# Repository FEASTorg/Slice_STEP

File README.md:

<div align="center">
  <!-- Title: -->
  
  <h2><a href="https://github.com/uwo-fast/Slice_STEP"> STEP Slice </a></h2>
  <!-- Labels: -->
  <!-- First row: -->

  <a href="https://certification.oshwa.org/">
    
    <!-- img src="https://img.shields.io/badge/OSHWA-Certified-darkgreen?style=flat-square" height="20" alt="OSHWA" -->       <!-- img src="https://img.shields.io/badge/OSHWA-Pending-darkorange?style=flat-square" height="20" alt="OSHWA" -->
  </a>

  <!-- Second row: -->
  <br>

  <!-- Short description: -->
  <h3>Stepper Motor Driver Carrier Slice for BREAD.</h3>
</div>

## Introduction
[Provide a brief introduction to the project, including the motivation and goals. Explain the significance and context of the research.]

## Project Overview
[Describe the project in more detail. This section can be split into subsections if necessary.]

## Ratings

Motor supply (VMOT, the board's M_POWER net) comes from one of two sources,
picked by a jumper on J5:

| J5 jumper | Drivers powered from | VMOT range |
| --- | --- | --- |
| pins 2-3 (OUT-12V) | BREAD bus +12V (J1 pins 2 and 9) | 12 V, as the bus supplies |
| pins 1-2 (CUSTOM-OUT) | CUSTOM PWR terminal J6 (+ pin 1, - pin 2) | 8-35 V |

J5 pin 1 is CUSTOM, pin 2 is M_POWER (OUT), pin 3 is +12V. Fit one jumper
only. No position ties the CUSTOM supply to the bus.

- 8-35 V is the A4988 carrier's motor supply range (Pololu #1182). The
  CUSTOM input's bypass capacitor C3 is rated 50 V (10 uF X7R).
- Every figure below is the total VMOT current of all four drivers
  together, not a per-driver figure (IPC-2221 estimate, 1 oz outer copper,
  20 C rise unless stated). All of it passes through the J5 jumper, so it
  is also capped by the rating of the shunt fitted there.
- 12 V mode: the bus feed's narrowest stretch is 1.0 mm, about 3.2 A
  (2.4 A for a 10 C rise).
- CUSTOM mode: the run from J6 pin 1 to J5 pin 1 is 1.5 mm, about 4.3 A.
- From J5 pin 2, M_POWER carries all four drivers through a 1.9 mm neck
  between J4 pin 8 and J5 pin 3 (about 5.2 A), then a pour at least 4.2 mm
  wide to C6 (drivers 1-3), then 2.5 mm to drivers 2 and 1. Each pin 8
  takes its own driver's current only.
- So the board carries about 3 A in total in 12 V mode and about 4 A in
  CUSTOM mode, shared by however many drivers run at once.

## Microstep mode

Each driver's step resolution is set by three solder jumpers on the back
of the board, beside that driver's MS1-MS3 pins (labelled MS1, MS2, MS3;
JP1-3 for driver 1 up to JP10-12 for driver 4). Closing a jumper ties that
pin to VDD (+5V). The A4988 pulls MS1-MS3 down internally, so an open
jumper reads low.

| MS1 | MS2 | MS3 | Step |
| --- | --- | --- | --- |
| open | open | open | full (default) |
| closed | open | open | 1/2 |
| open | closed | open | 1/4 |
| closed | closed | open | 1/8 |
| closed | closed | closed | 1/16 |

The Nano does not drive these pins: A6 and A7 are analog-input-only on the
ATmega328P, and D13 is left free.

## Installation
[Provide instructions for installing any necessary software or hardware components.]

## Usage
[Explain how to use the project. Include examples and screenshots if applicable.]

### Basic Usage
[Provide basic usage instructions.]

### Advanced Usage
[Provide advanced usage instructions, including any optional features or configurations.]

## Documentation
[Link to the detailed documentation if available. Provide instructions on how to access and navigate the documentation.]

## Contributing
[Explain how others can contribute to the project. Include guidelines for submitting issues, pull requests, and any coding standards.]

### Code of Conduct
[Link to the project's code of conduct if available.]

## License
[State the license under which the project is distributed. Include a link to the full license text.]

## Acknowledgements
[Acknowledge any contributors, collaborators, funding sources, or organizations that supported the project.]

## Contact
[Provide contact information for the project maintainer(s) or lead researcher(s). Include an email address or a link to a contact form.]

---

<div align="center">
  
</div>

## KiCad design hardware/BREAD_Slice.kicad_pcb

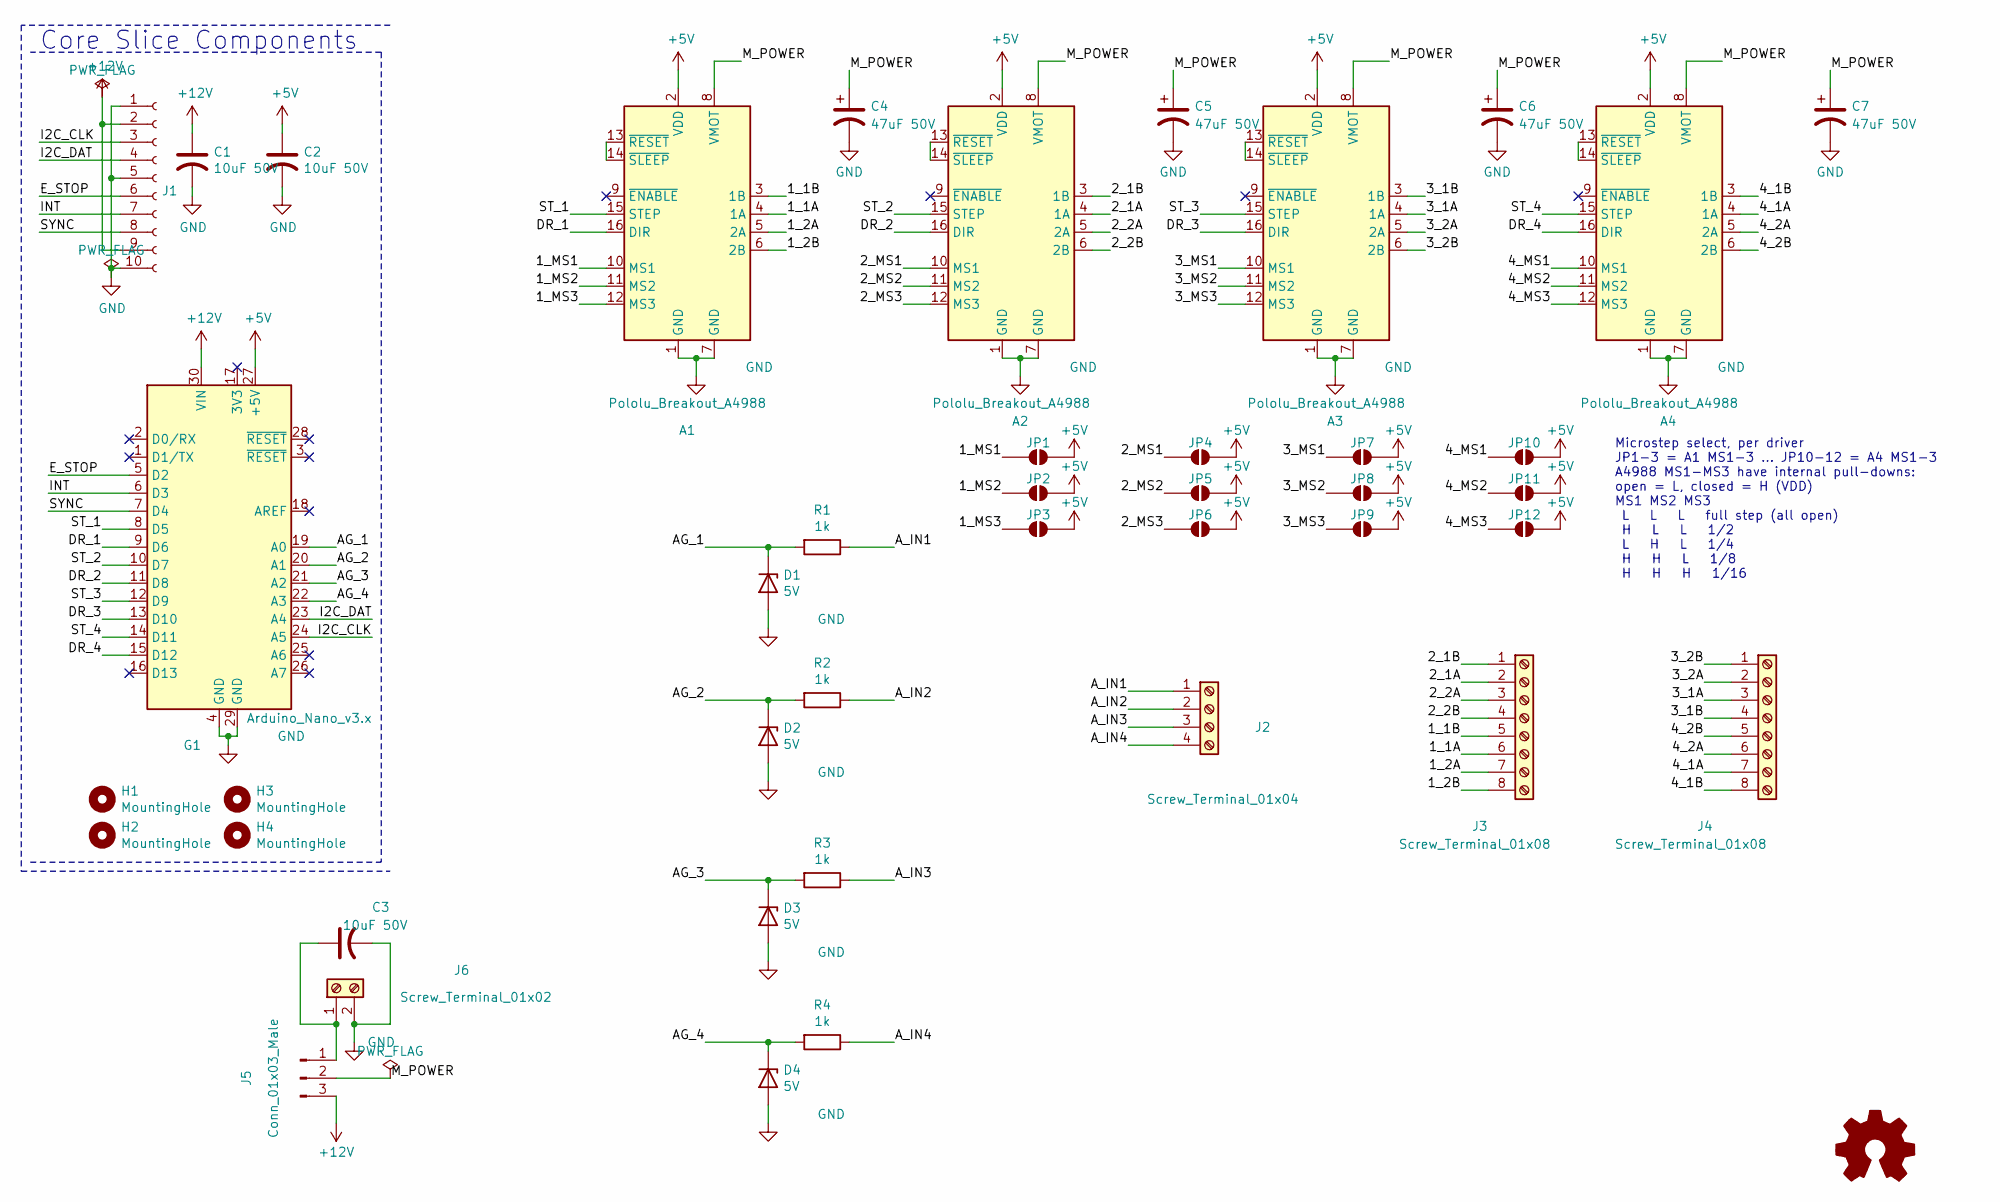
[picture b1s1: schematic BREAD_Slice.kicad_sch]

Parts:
A1, A2, A3, A4: Pololu_Breakout_A4988; Pololu_Breakout-16_15.2x20.3mm
C1, C2, C3: 10uF 50V; C_1210_3225Metric; Part # CL32B106KBJNNNE
C4, C5, C6, C7: 47uF 50V; CP_Elec_6.3x7.7; Part # EEE-FK1H470XP
D1, D2, D3, D4: 5V; D_1206_3216Metric_Pad1.42x1.75mm_HandSolder
G1: Arduino_Nano_v3.x; Arduino_Nano
H1, H2, H3, H4: MountingHole; MountingHole_5mm
J1: Conn_01x10_Female; PinSocket_1x10_P2.54mm_Horizontal
J2: Screw_Terminal_01x04; TerminalBlock_TE_282834-4_1x04_P2.54mm_Horizontal
J3, J4: Screw_Terminal_01x08; TerminalBlock_TE_282834-8_1x08_P2.54mm_Horizontal
J5: Conn_01x03_Male; PinSocket_1x03_P2.54mm_Vertical
J6: Screw_Terminal_01x02; TerminalBlock_TE_282834-2_1x02_P2.54mm_Horizontal
JP1, JP2, JP3, JP4, JP5, JP6, JP7, JP8, JP9, JP10, JP11, JP12: SolderJumper_2_Open; SolderJumper-2_P1.3mm_Open_RoundedPad1.0x1.5mm
Logo1: Logo_Open_Hardware_Small; OSHW-Symbol_6.7x6mm_SilkScreen
R1, R2, R3, R4: 1k; R_1206_3216Metric_Pad1.30x1.75mm_HandSolder

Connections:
+5V: A1.2 (VDD), A2.2 (VDD), A3.2 (VDD), A4.2 (VDD), C2.1, G1.27 (+5V), JP1.2 (B), JP2.2 (B), JP3.2 (B), JP4.2 (B), JP5.2 (B), JP6.2 (B), JP7.2 (B), JP8.2 (B), JP9.2 (B), JP10.2 (B), JP11.2 (B), JP12.2 (B)
+12V: C1.1, G1.30 (VIN), J1.2, J1.9, J5.3
/1_1A: A1.4 (1A), J3.6
/1_1B: A1.3 (1B), J3.5
/1_2A: A1.5 (2A), J3.7
/1_2B: A1.6 (2B), J3.8
/1_MS1: A1.10 (MS1), JP1.1 (A)
/1_MS2: A1.11 (MS2), JP2.1 (A)
/1_MS3: A1.12 (MS3), JP3.1 (A)
/2_1A: A2.4 (1A), J3.2
/2_1B: A2.3 (1B), J3.1
/2_2A: A2.5 (2A), J3.3
/2_2B: A2.6 (2B), J3.4
/2_MS1: A2.10 (MS1), JP4.1 (A)
/2_MS2: A2.11 (MS2), JP5.1 (A)
/2_MS3: A2.12 (MS3), JP6.1 (A)
/3_1A: A3.4 (1A), J4.3
/3_1B: A3.3 (1B), J4.4
/3_2A: A3.5 (2A), J4.2
/3_2B: A3.6 (2B), J4.1
/3_MS1: A3.10 (MS1), JP7.1 (A)
/3_MS2: A3.11 (MS2), JP8.1 (A)
/3_MS3: A3.12 (MS3), JP9.1 (A)
/4_1A: A4.4 (1A), J4.7
/4_1B: A4.3 (1B), J4.8
/4_2A: A4.5 (2A), J4.6
/4_2B: A4.6 (2B), J4.5
/4_MS1: A4.10 (MS1), JP10.1 (A)
/4_MS2: A4.11 (MS2), JP11.1 (A)
/4_MS3: A4.12 (MS3), JP12.1 (A)
/AG_1: D1.1 (K), G1.19 (A0), R1.2
/AG_2: D2.1 (K), G1.20 (A1), R2.2
/AG_3: D3.1 (K), G1.21 (A2), R3.2
/AG_4: D4.1 (K), G1.22 (A3), R4.2
/A_IN1: J2.1, R1.1
/A_IN2: J2.2, R2.1
/A_IN3: J2.3, R3.1
/A_IN4: J2.4, R4.1
/DR_1: A1.16 (DIR), G1.9 (D6)
/DR_2: A2.16 (DIR), G1.11 (D8)
/DR_3: A3.16 (DIR), G1.13 (D10)
/DR_4: A4.16 (DIR), G1.15 (D12)
/E_STOP: G1.5 (D2), J1.6
/I2C_CLK: G1.24 (A5), J1.3
/I2C_DAT: G1.23 (A4), J1.4
/INT: G1.6 (D3), J1.7
/M_POWER: A1.8 (VMOT), A2.8 (VMOT), A3.8 (VMOT), A4.8 (VMOT), C4.1, C5.1, C6.1, C7.1, J5.2
/ST_1: A1.15 (STEP), G1.8 (D5)
/ST_2: A2.15 (STEP), G1.10 (D7)
/ST_3: A3.15 (STEP), G1.12 (D9)
/ST_4: A4.15 (STEP), G1.14 (D11)
/SYNC: G1.7 (D4), J1.8
GND: A1.1 (GND), A1.7 (GND), A2.1 (GND), A2.7 (GND), A3.1 (GND), A3.7 (GND), A4.1 (GND), A4.7 (GND), C1.2, C2.2, C3.2, C4.2, C5.2, C6.2, C7.2, D1.2 (A), D2.2 (A), D3.2 (A), D4.2 (A), G1.4 (GND), G1.29 (GND), J1.1, J1.5, J1.10, J6.2
unnamed: A1.13 (~RESET), A1.14 (~SLEEP)
unnamed: A2.13 (~RESET), A2.14 (~SLEEP)
unnamed: A3.13 (~RESET), A3.14 (~SLEEP)
unnamed: A4.13 (~RESET), A4.14 (~SLEEP)
unnamed: C3.1, J5.1, J6.1

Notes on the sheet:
Core Slice Components
Microstep select, per driver JP1-3 = A1 MS1-3 ... JP10-12 = A4 MS1-3 A4988 MS1-MS3 have internal pull-downs: open = L, closed = H (VDD) MS1 MS2 MS3 L L L full step (all open) H L L 1/2 L H L 1/4 H H L 1/8 H H H 1/16

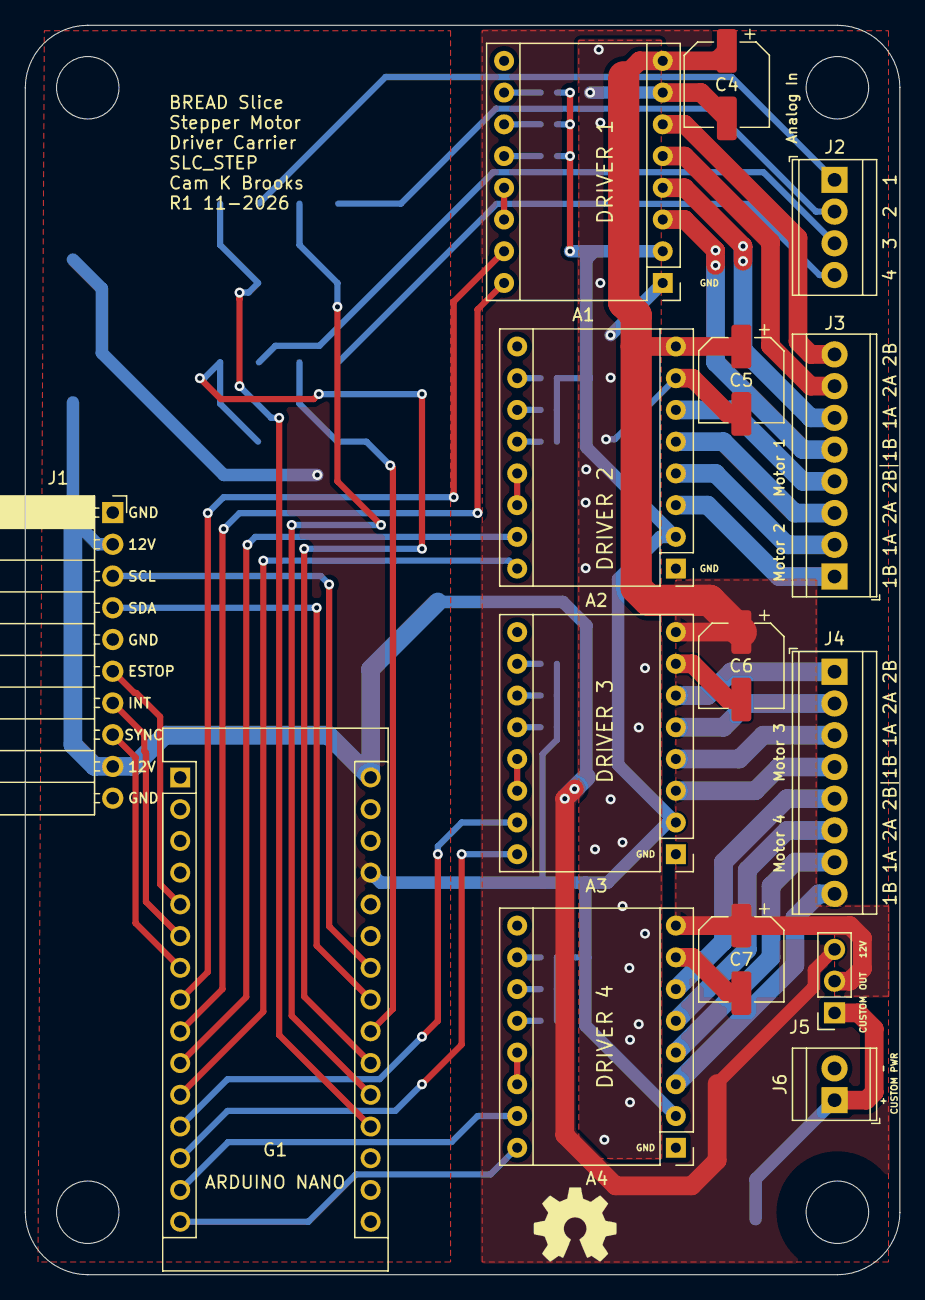
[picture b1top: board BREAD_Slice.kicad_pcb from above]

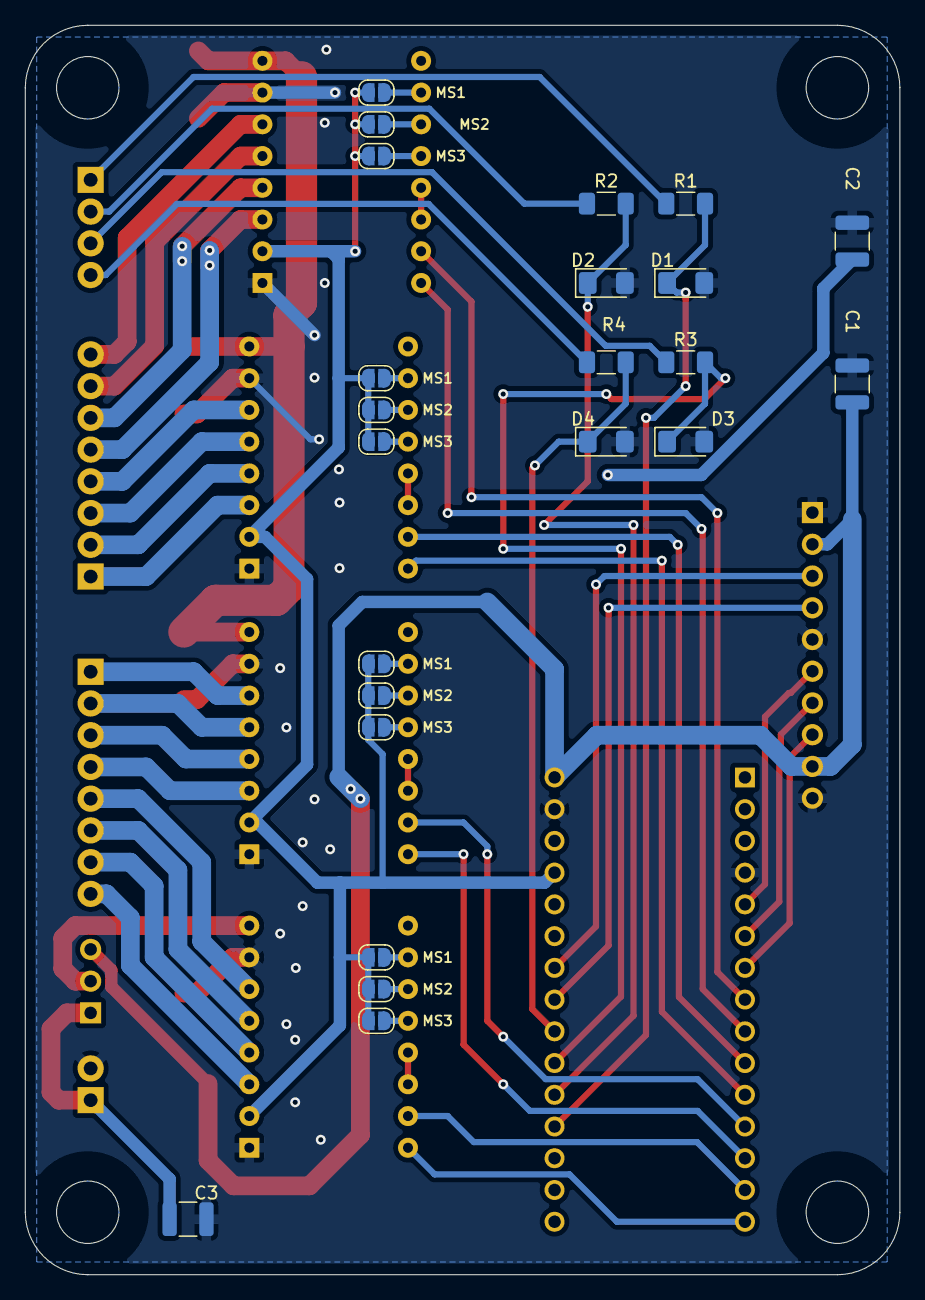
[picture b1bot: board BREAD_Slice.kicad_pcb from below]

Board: 2 copper layers, 70.0 x 100.0 mm, 43 parts (23 on the bottom side), 58 nets.

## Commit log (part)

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2024-05-23 Initial commmit
2025-04-19 minor tweaks
2026-04-18 chore: revisions to step board
2026-05-20 Add slice.yaml manifest (schema v1.0)
2026-05-24 Add KiBot/docs pipeline
2026-05-24 Update TODO with CI findings
2026-05-24 Standardize TODO.md with Pass 1/Pass 2 structure
